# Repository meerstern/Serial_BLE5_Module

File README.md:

# Serial_BLE5_Module
BGX13P module board

## 告知
  * メーカ側でBGX13Pの生産終了が告知されたため、23年4月以降は在庫限りです  
  * 23年4月以降の新ロット製作の予定はありません  
  * 新規開発の採用には適しません  
  * [後継機種][6]への移行を検討してください  

## 概要 
  * SiliconLabs製BLE5モジュールBGX13Pを搭載した変換基板です。
  * BLE5の制御ソフトウェアが予め書き込まれているため、容易にBluetooh通信を使⽤できます。
  * スマートフォンや他のBGX13Pと容易に接続することが可能です。
  * 3.3Vシリアル通信(UART,初期115200bps)で外部機器からパラメータを設定できます。  
  * 3.3Vシリアル通信はGROVEコネクタでも接続できます。  
  * 基板上からBGX13PすべてのIOにアクセスできます。  
  * TELEC(技適)認証済 工事設計認証番号 [209-J00282][5]

## 販売サイト
  * [スイッチサイエンス][7]

## 関連情報
 * [データシート][1]
 * [SiliconLabs製品サイト][2]
 * マクニカ製品紹介サイト[その１][3]、[その２][4]  

[1]: https://www.silabs.com/documents/public/data-sheets/bgx13p-datasheet.pdf "*1"
[2]: https://jp.silabs.com/products/wireless/bluetooth/xpress "*2"

[3]: https://service.macnica.co.jp/library/130293 "*3"
[4]: https://service.macnica.co.jp/library/130269 "*4"
[5]: https://www.tele.soumu.go.jp/giteki/SearchServlet?pageID=jg01_01&PC=209&TC=N&PK=1&FN=190710N209&SN=%94%46%8F%D8&LN=3&R1=*****&R2=***** "*5"
[6]: https://github.com/meerstern/Serial_BLE5_Module_V2 "*6"

[7]: https://www.switch-science.com/products/5794

MIT Lisense

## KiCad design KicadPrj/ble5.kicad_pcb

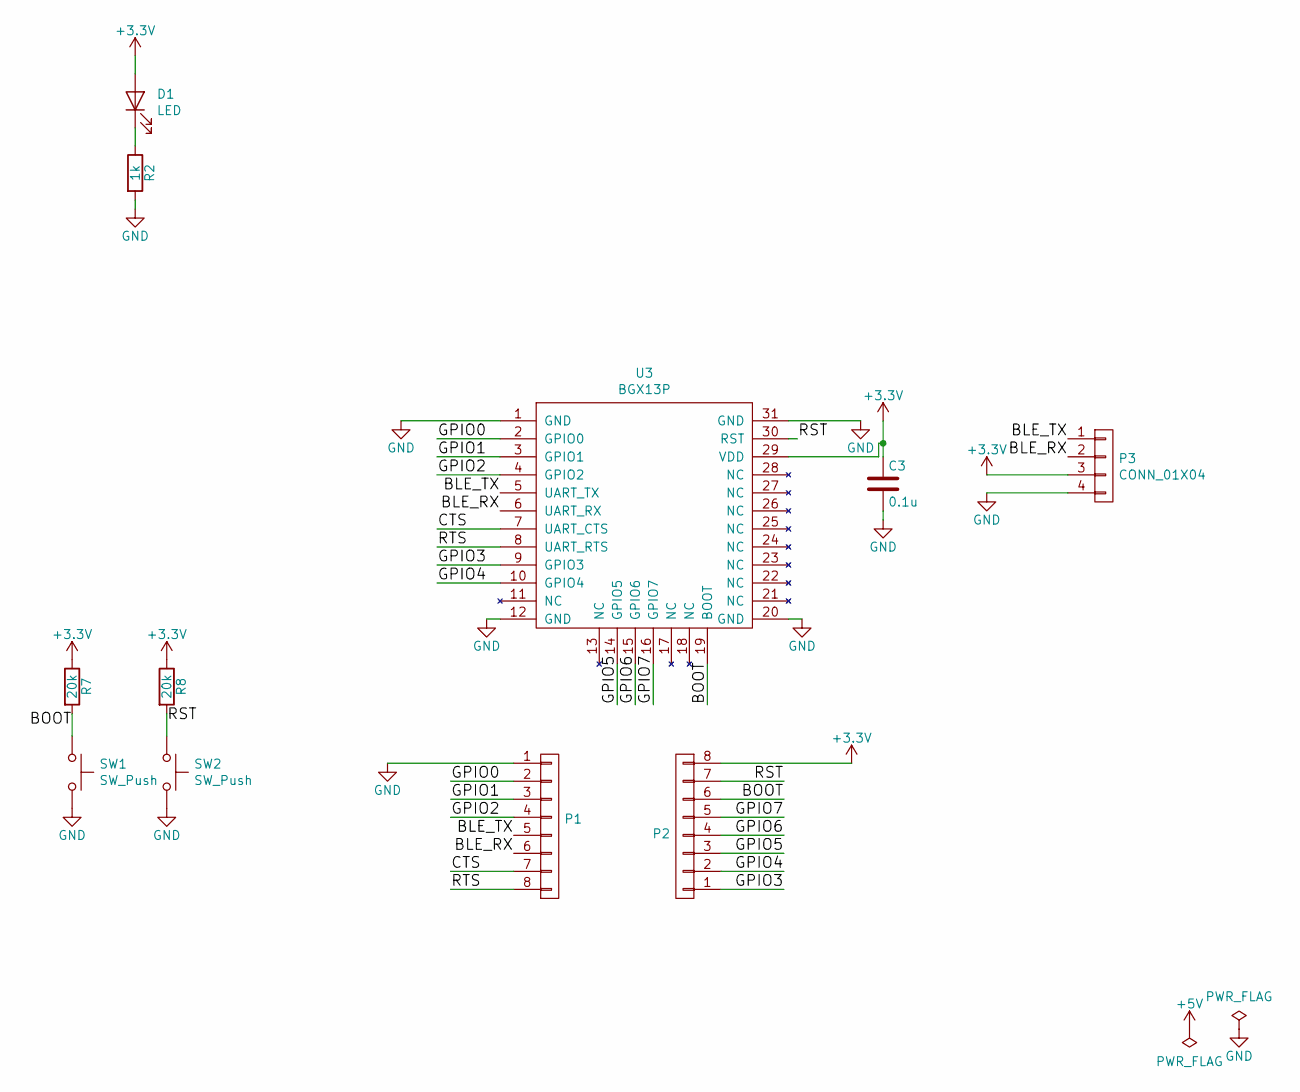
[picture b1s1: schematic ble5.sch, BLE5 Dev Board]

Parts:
C3: 0.1u; C-0603
D1: LED; generic-LED1608
P1, P2: CONN_01X08; pinhead-1X08
P3: CONN_01X04; GROVE
R2: 1k; R-0603
R7, R8: 20k; R-0603
SW1, SW2: SW_Push; SKRPACE010
U3: BGX13P; bgm13p-smd

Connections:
+3V3: C3.1, D1.A, P2.8, P3.3, R7.1, R8.1, U3.29 (VDD)
/BLE_RX: P1.6, P3.2, U3.6 (UART_RX)
/BLE_TX: P1.5, P3.1, U3.5 (UART_TX)
/BOOT: P2.6, R7.2, SW1.1, U3.19 (BOOT)
/CTS: P1.7, U3.7 (UART_CTS)
/GPIO0: P1.2, U3.2 (GPIO0)
/GPIO1: P1.3, U3.3 (GPIO1)
/GPIO2: P1.4, U3.4 (GPIO2)
/GPIO3: P2.1, U3.9 (GPIO3)
/GPIO4: P2.2, U3.10 (GPIO4)
/GPIO5: P2.3, U3.14 (GPIO5)
/GPIO6: P2.4, U3.15 (GPIO6)
/GPIO7: P2.5, U3.16 (GPIO7)
/RST: P2.7, R8.2, SW2.1, U3.30 (RST)
/RTS: P1.8, U3.8 (UART_RTS)
GND: C3.2, P1.1, P3.4, R2.2, SW1.2, SW2.2, U3.1 (GND), U3.12 (GND), U3.20 (GND), U3.31 (GND)
unnamed: D1.K, R2.1

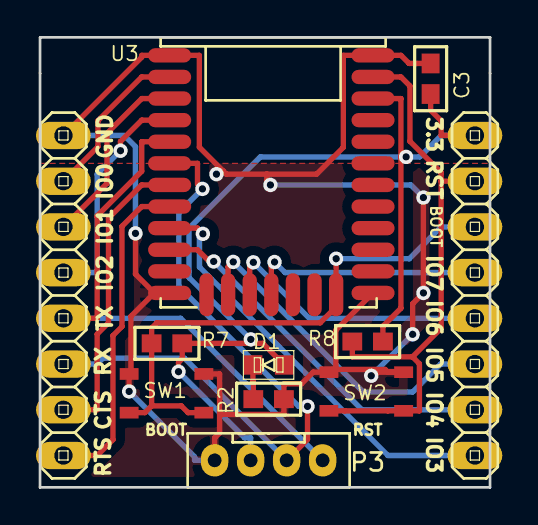
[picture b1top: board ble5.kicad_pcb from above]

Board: 2 copper layers, 25.0 x 25.0 mm, 11 parts (0 on the bottom side), 17 nets.

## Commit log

2019-06-28 Upload the kicad project
2019-06-28 Add images
2019-07-06 Add README
2019-07-31 Add PDF Data
